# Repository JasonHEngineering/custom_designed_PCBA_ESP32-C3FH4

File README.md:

# Custom PCBA design

I have designed and fabricated a custom board with ESP32-C3 with the following key hardware features:

- Using ESP32-C3FH4 (embedded flash memory)
- Power management from USB as well as from (maximum) 12 V source (LDO: AMS1117-3.3 and L78L05ABUTR)
- Stepper motor driver (DRV8825)
- Accelerometer + Gyro unit (MPU6050)
- Built-in 2.4 GHz inverted F antenna (reference)
- CAN transceiver (TJA1051T/CM,118)

Project Layout build from KiCad 6:
Refer to folder "KiCad Project Schematics and Gerbers"

## Layout snapshot

## Actual 

Scope of sample codes under folder names:
BLE_Advertising_example_V1 - BLE advertising example
BLE_Gyro_example_V2 - Gyro data sent over BLE from custom board to phone with nRF app
Custom_ESP32_DRV8825_V1 - Stepper motor driving with on board DRV8825
ESP32_custom_board_LED_flash_V1 - Initial program sanity check if the MCU is working
MP6050_trial_V2 - Grab data from gyroscope/accelrometer
SimpleWiFiServer - Becomes a web server to trigger a GPIO action (e.g. LED)
Wifi_scan_example - Scan the wifi network and check for RSSI signal strength 

## Example GIFs

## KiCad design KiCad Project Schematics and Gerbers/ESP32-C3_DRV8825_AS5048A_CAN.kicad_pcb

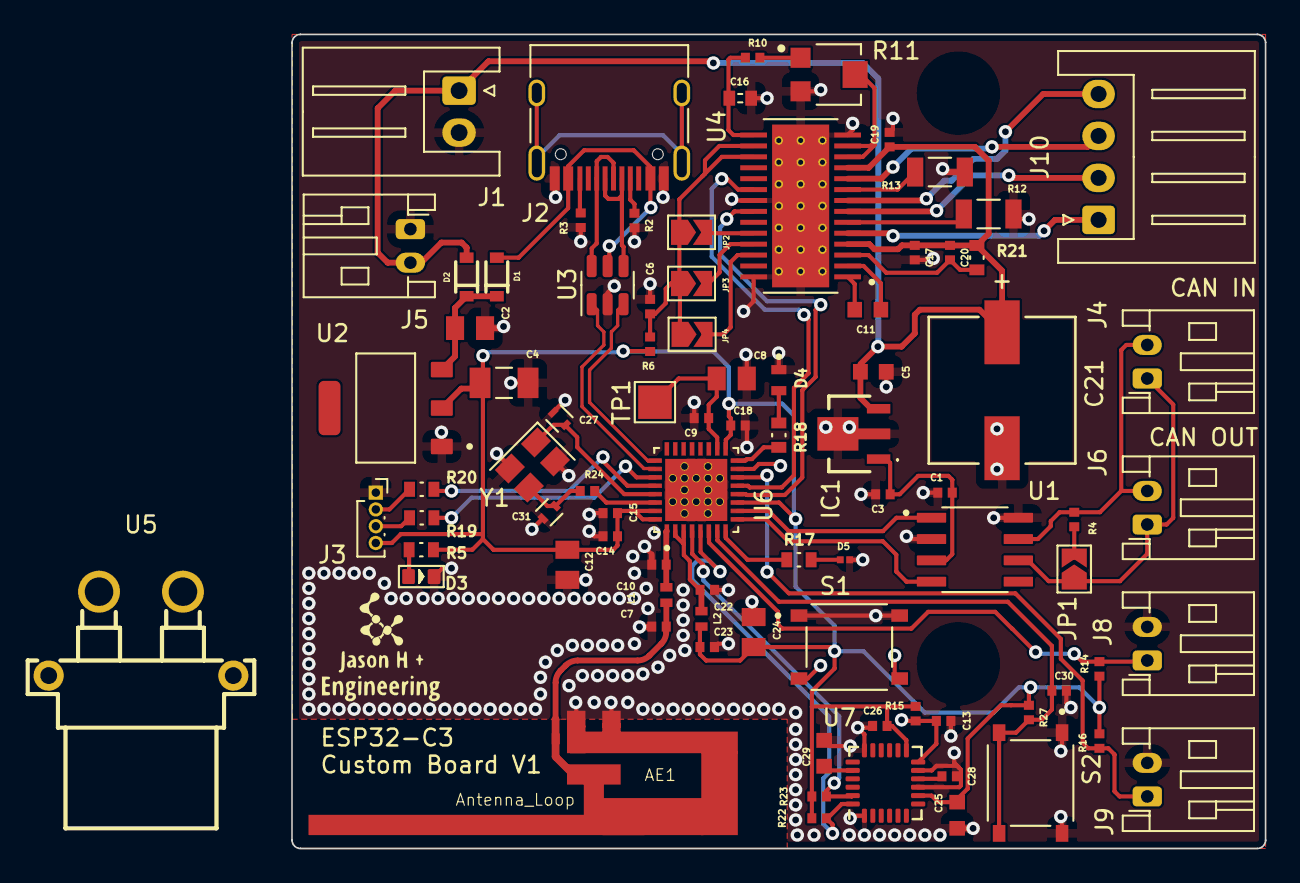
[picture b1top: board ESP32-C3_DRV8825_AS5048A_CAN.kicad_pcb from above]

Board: 4 copper layers, 58.0 x 48.5 mm, 85 parts (0 on the bottom side), 59 nets.

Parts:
AE1: Antenna_Loop; 2.4GHz-INVERTED-F-ANTENNA
C1, C3, C6, C9, C13, C14, C15, C17, C18, C19, C20, C22, C23, C26, C28, C30: GCM155R71C104KA55J; CAPC1005X55N
C2, C8, C12, C24: GRM21BR61E106KA73L; CAPC2012X140N
C4: GRM31CR71A226KE15L; CAPC3216X180N
C5: GCM188R71C334KA37D; CAPC1608X90N
C7, C10: GJM1555C1H3R3BB01D; CAPC1005X55N
C11, C25: CL10B103KB8NNNC; CAPC1608X90N
C16: GRM155B31A474KE14D; INDC1005X45
C21: 100uF; PCAP_8X10-ELECT
C27, C31: CL10C100JB8NNNC; CAPC1005X55N
C29: GCM1885C1H222JA16D; CAPC1608X90N
D1, D2: BAT20JFILM; SOD-323
D3: SMD-LED-CLEAR-BLUE(0603); LED-0603
D4: 19-213/R6C-AP1Q2B/3T; LED_19-213_R6C-AP1Q2B_3T
D5: SZYY0402W; CAPC0603X39N
IC1: L78L05ABUTR
J1: Conn_01x02_Female; JST_XH_S2B-XH-A_1x02_P2.50mm_Horizontal
J2: USB_C_Receptacle_USB2.0; USB_C_Receptacle_HRO_TYPE-C-31-M-12
J3: Conn_01x04_Female; PinSocket_1x04_P1.00mm_Vertical
J4, J5, J6, J8, J9: Conn_01x02_Female; JST_PH_S2B-PH-K_1x02_P2.00mm_Horizontal
J10: Conn_01x04_Female; JST_XH_S4B-XH-A_1x04_P2.50mm_Horizontal
JP1, JP2, JP3, JP4: Jumper_2_Open; SolderJumper-2_P1.3mm_Open_TrianglePad1.0x1.5mm
L1, L2: LQW15AN2N2G80D; INDC1006X60N
R2, R3, R6, R10, R14, R15, R16, R22, R23, R27: RC0402FR-075K1L; RESC1005X40N
R4: RC0402FR-07120RL; RESC1005X40N
R5, R17, R18, R19, R20: ERJ3EKF4700V; RES_ERJ3EKF4700V
R11: TC33X-2-103E; TRIM_TC33X-2-103E
R12, R13: RL1206JR-070R2L; RESC3116X65N
R21: ERJ3EKF1004V; RES_ERJ3EKF1004V
R24: AC0402FR-0722RL; RESC1005X37N
S1, S2: TS-1187A-B-A-B; SW_TS-1187A-B-A-B
TP1: TestPoint; TestPoint_Pad_2.0x2.0mm
U1: TJA1051T/CM,118; SOIC127P600X175-8N
U2: AMS1117-3.3; SOT229P700X180-4N
U3: USBLC6-2SC6; SOT-23-6
U4: DRV8825PWPR; IC_TPS61196PWPRQ1
U5: XT30PW-F; CONN-TH_XT30PW-F-1
U6: ESP32-C3FH4; QFN50P500X500X90-33N
U7: MPU-6050; InvenSense_QFN-24_4x4mm_P0.5mm
Y1: 40MHz 9pF ±10ppm SMD3225-4P; Crystal_SMD_SeikoEpson_TSX3225-4Pin_3.2x2.5mm

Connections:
/3V3: C4.1, C12.1, C14.1, C15.1, C18.1, C23.1, C24.1, C25.1, C26.1, J3.4, L2.2, R5.1, R6.1, R14.1, R15.1, R16.1, R22.1, R23.1, R27.1, U2.2 (VOUT), U6.11 (VDD3P3_RTC), U6.17 (VDD3P3_CPU), U6.31 (VDDA), U6.32 (VDDA), U7.8 (VDDIO), U7.13 (VDD)
/3v3_ref: C16.1, R10.1, U4.15 (V3P3OUT)
/5V_CAN: C1.1, C3.1, IC1.1 (VOUT), U1.3 (VCC)
/5V_USB: D1.A, J2.A4 (VBUS), J2.A9 (VBUS), J2.B4 (VBUS), J2.B9 (VBUS), U3.5 (VBUS)
/12V: C5.1, C17.1, C19.1, C20.1, C21.1, D2.A, IC1.3 (VIN), J1.1, J5.2, R21.1, U4.4 (VMA), U4.11 (VMB)
/+3V3_RF: C22.1, L2.1, U6.2 (VDD3P3), U6.3 (VDD3P3)
/Antenna: C10.1, L1.2, U6.1 (LNA_IN)
/CAN_H: J4.2, J6.2, R4.2, U1.7 (CANH)
/CAN_L: J4.1, J6.1, JP1.1 (A), U1.6 (CANL)
/CAN_RX_N: U1.4 (RXD), U6.9 (MTMS)
/CAN_TX_P: U1.1 (TXD), U6.10 (MTDI)
/DIR: U4.20 (DIR), U6.13 (MTDO)
/INT_ACC: C13.1, R15.2, S1.C, S1.D, U6.15 (GPIO9), U7.12 (INT)
/LED1: R17.1, U6.8 (GPIO3)
/LED2: R18.1, U6.16 (GPIO10)
/M11: J10.1, U4.5 (AOUT1)
/M12: J10.2, U4.7 (AOUT2)
/M13: J10.3, U4.10 (BOUT1)
/M14: J10.4, U4.8 (BOUT2)
/MC0: JP2.2 (B), U4.24 (MODE0)
/MC1: JP3.2 (B), U4.25 (MODE1)
/MC2: JP4.2 (B), U4.26 (MODE2)
/MCU_USB_D_N: U3.3 (I/O2), U6.25 (GPIO18)
/MCU_USB_D_P: U3.1 (I/O1), U6.26 (GPIO19)
/SCL_ACC: R23.2, U6.4 (XTAL_32K_P), U7.23 (SCL)
/SDA_ACC: R22.2, U6.5 (XTAL_32K_N), U7.24 (SDA)
/SET_HIGH: C6.1, JP2.1 (A), JP3.1 (A), JP4.1 (A), R6.2, U4.16 (~NRESET), U4.17 (NSLEEP)
/STP: U4.22 (STEP), U6.12 (MTCK)
/UART0_RX: J3.3, R19.2
/UART0_TX: J3.2, R20.2
/USB_D_N: J2.A7 (D-), J2.B7 (D-), U3.4 (I/O2)
/USB_D_P: J2.A6 (D+), J2.B6 (D+), U3.6 (I/O1)
/VCP: C20.2, R21.2, U4.3 (VCP)
/VDD_SPI: C8.1, C9.1, TP1.1, U6.18 (VDD_SPI)
GND: AE1.2, C1.2, C2.2, C3.2, C4.2, C5.2, C6.2, C7.2, C8.2, C9.2, C10.2, C12.2, C13.2, C14.2, C15.2, C16.2, C17.2, C18.2, C19.2, C21.2, C22.2, C23.2, C24.2, C25.2, C26.2, C27.2, C28.2, C29.2, C30.2, C31.2, D3.-, D4.1, D5.2, IC1.2 (GND_1), IC1.4 (GND_2), J1.2, J2.A1 (GND), J2.A12 (GND), J2.B1 (GND), J2.B12 (GND), J3.1, J5.1, J8.2, J9.2, R2.2, R3.2, R11.3, R12.2, R13.2, S1.A, S1.B, S2.A, S2.B, U1.2 (GND), U1.8 (S), U2.1 (GND/ADJ), U3.2 (GND), U4.14 (GND), U4.21 (NENBL), U4.28 (GND), U6.33 (GND), U7.1 (CLKIN), U7.9 (AD0), U7.11 (FSYNC), U7.18 (GND), Y1.2 (GND), Y1.4 (GND)
unnamed: AE1.1, C7.1, L1.1
unnamed: C2.1, D1.C, D2.C, U2.3 (VIN)
unnamed: C11.1, U4.1 (CP1)
unnamed: C11.2, U4.2 (CP2)
unnamed: C27.1, U6.29 (XTAL_N), Y1.1
unnamed: C28.1, U7.10 (REGOUT)
unnamed: C29.1, U7.20 (CPOUT)
unnamed: C30.1, R27.2, S2.C, S2.D, U6.7 (CHIP_EN)
unnamed: C31.1, R24.2, Y1.3
unnamed: D3.+, R5.2
unnamed: D4.2, R18.2
unnamed: D5.1, R17.2
unnamed: J2.A5 (CC1), R2.1
unnamed: J2.B5 (CC2), R3.1
unnamed: J8.1, R14.2, U6.6 (GPIO2)
unnamed: J9.1, R16.2, U6.14 (GPIO8)
unnamed: JP1.2 (B), R4.1
unnamed: R10.2, R11.1
unnamed: R11.2, U4.12 (AVREF), U4.13 (BVREF)
unnamed: R12.1, U4.6 (ISENA)
unnamed: R13.1, U4.9 (ISENB)
unnamed: R19.1, U6.27 (U0RXD)
unnamed: R20.1, U6.28 (U0TXD)
unnamed: R24.1, U6.30 (XTAL_P)

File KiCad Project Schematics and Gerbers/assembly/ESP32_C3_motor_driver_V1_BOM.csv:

Comment,Designator,Footprint,LCSC
Antenna_Loop,AE1,RF_Antenna_downloaded:2.4GHz-INVERTED-F-ANTENNA,
GCM155R71C104KA55J,"C1,C3,C6,C9,C13,C14,C15,C17,C18,C19,C20,C22,C23,C26,C28,C30",100nf_cap_GCM155R71C104KA55J:CAPC1005X55N,C84416
CL10B103KB8NNNC,"C11,C25",10nF_cap_CL10B103KB8NNNC:CAPC1608X90N,C2655418
LMK063BC6474KPLF,C16,470nf_cap_LMK063BC6474KPLF:CAPC0603X39N,C91604
GRM21BR61E106KA73L,"C2,C8,C12,C24",10uF_cap_GRM21BR61E106KA73L:CAPC2012X140N,C144384
UWT1H101MNL1GS,C21,100uF_cap_UWT1H101MNL1GS:PCAP_8X10-ELECT,C76906
CL05C100JB5NNNC,"C27,C31",10pF_cap_CL05C100JB5NNNC:CAPC1005X55N,C2169138
GCM1885C1H222JA16D,C29,2200pF_cap_GCM1885C1H222JA16D:CAPC1608X90N,C445063
GRM31CR71A226KE15L,C4,22uF_cap_GRM31CR71A226KE15L:CAPC3216X180N,C1589
GCM188R71C334KA37D,C5,330nF_cap_GCM188R71C334KA37D:CAPC1608X90N,C343869
GJM1555C1H3R3BB01D,"C7,C10",3p3_RF_cap_GJM1555C1H3R3BB01D:CAPC1005X55N,C32949
BAT20JFILM,"D1,D2",diode_BAT20JFILM:SOD-323,C155590
SMD-LED-CLEAR-BLUE(0603),D3,Blue_LED_SMD-LED-CLEAR-BLUE_0603:LED-0603,C72041
19-213/R6C-AP1Q2B/3T,D4,Red_LED_19-213R6C-AP1Q2B3T:LED_19-213_R6C-AP1Q2B_3T,C128051
19-213SYGC/S530-E2/TR8,D5,Yellow_Green_LED_19-213SYGCS530-E2TR8:CAPC0603X39N,C409444
L78L05ABUTR,IC1,LDO_L78L05ABUTR_5V:L78L05ABUTR,C42738
Conn_01x02_Female,J1,Connector_JST:JST_XH_S2B-XH-A_1x02_P2.50mm_Horizontal,C157931
Conn_01x04_Female,J10,Connector_JST:JST_XH_S4B-XH-A_1x04_P2.50mm_Horizontal,C165948
USB_C_Receptacle_USB2.0,J2,Connector_USB:USB_C_Receptacle_HRO_TYPE-C-31-M-12,
Conn_01x04_Female,J3,Connector_PinSocket_1.00mm:PinSocket_1x04_P1.00mm_Vertical,C173752
Conn_01x02_Female,"J4,J5,J6,J8,J9",Connector_JST:JST_PH_S2B-PH-K_1x02_P2.00mm_Horizontal,C157925
Jumper_2_Open,"JP1,JP2,JP3,JP4",solder_jumpers:SolderJumper-2_P1.3mm_Open_TrianglePad1.0x1.5mm,
LQW15AN2N2G80D,"L1,L2",2n2_RF_inductor_LQW15AN2N2G80D:INDC1006X60N,C412264
TC33X-2-103E,R11,10k_pot_TC33X-2-103E:TRIM_TC33X-2-103E,C114758
RL1206JR-070R2L,"R12,R13",200mR_RL1206JR-070R2L:RESC3116X65N,C169259
RC0402FR-075K1L,"R2,R3,R6,R10,R14,R15,R16,R22,R23,R27",5.1kR_RC0402FR-075K1L:RESC1005X40N,C719176
ERJ3EKF1004V,R21,1MR_ERJ3EKF1004V:RES_ERJ3EKF1004V,C327155
AC0402FR-0722RL,R24,22R_AC0402FR-0722RL:RESC1005X37N,C105872
RC0402FR-07120RL,R4,120R_RC0402FR-07120RL:RESC1005X40N,C193390
ERJ3EKF4700V,"R5,R17,R18,R19,R20",470R_ERJ3EKF4700V:RES_ERJ3EKF4700V,C226359
TS-1187A-B-A-B,"S1,S2",Tact_switch_TS-1187A-B-A-B:SW_TS-1187A-B-A-B,C318884
TestPoint,TP1,TestPoint:TestPoint_Pad_2.0x2.0mm,
"TJA1051T/CM,118",U1,CAN_tranceiver_TJA1050T_CM_118:SOIC127P600X175-8N,C2859133
AMS1117-3.3,U2,LDO_AMS1117-3v3:SOT229P700X180-4N,C6186
USBLC6-2SC6,U3,Package_TO_SOT_SMD:SOT-23-6,C7519
DRV8825PWPR,U4,stepper_driver_DRV8825.pretty:IC_TPS61196PWPRQ1,C81582
ESP32-C3FH4,U6,ESP32-C3FH4:QFN50P500X500X90-33N,C2858491
MPU-6050,U7,Sensor_Motion:InvenSense_QFN-24_4x4mm_P0.5mm, C24112 
40MHz 9pF ±10ppm SMD3225-4P,Y1,crystal_footprints:Crystal_SMD_SeikoEpson_TSX3225-4Pin_3.2x2.5mm,C255943

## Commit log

2025-08-24 Initial upload
    Initial upload - KiCad 6 project, schematics and gerbers
2025-08-24 Sample Codes Upload
    Sample Codes Upload
